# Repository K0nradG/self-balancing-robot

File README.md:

# Self-Balancing Robot

A two-wheeled self-balancing robot built around the **Nordic nRF52840** and
**Zephyr RTOS**, using **nRF Connect SDK 2.8.0**. The project includes the
embedded control system, custom electronics and mechanical designs, a BLE
desktop application, over-the-air firmware updates, and tools for modelling
and controller development.

## Documentation

- [Project overview](README.md)
- [Environment setup](docs/environment_setup.md)
- [Building and flashing](docs/building_and_running_fw.md)
- [BLE protocol](Sources/drivers/bluetooth/README.md)
- [Control-loop structure](Sources/robot_control/docs/control_loop.md)
- [Application state machine](Sources/robot_control/docs/application_state_machine.md)
- [Mathematical model](mathematical_model/doc/model.md)

## Demonstration

https://github.com/user-attachments/assets/bdc0d3e3-bf6b-4125-bade-0684ad42b085

> 🎥 **See the robot in action!** 
> Check out the [Lapun Embedded Control Lab](https://youtube.com/@lapunembededcontrollab) on YouTube for more demonstrations.
>
> 

## Features

### Robot firmware

- Cascaded control loop for balancing, driving, and rotation
- PID controllers with user-adjustable setpoints and parameters
- Optional LQR balance controller
- Trajectory generation for linear motion and rotation
- MPU6050 inertial measurement and quadrature encoder feedback
- PWM motor control through a dual-channel TB6612FNG driver
- Battery-voltage monitoring
- Safety angle validation and controlled motor shutdown
- Binary BLE protocol for commands, telemetry, and diagnostic logs
- MCUboot-based device firmware update over BLE

### Control and development tools

- PyQt6 desktop application for BLE control, live telemetry, PID tuning, and DFU
- Offline model identification and LQR tuning tools
- MATLAB/Simulink models of the inverted-pendulum system
- Optional Raspberry Pi Zero 2 W web interface with camera streaming
- KiCad schematics, PCB layout, Gerber files, and mechanical CAD

> [!NOTE]
> The default firmware configuration uses PID control. The LQR controller and
> on-device model-identification mode are implemented but disabled by default.
>
> The Raspberry Pi web interface and the nRF7002 DK controller are legacy or
> experimental components and may require adaptation to the current binary BLE
> protocol.

## Control architecture

The firmware uses a cascaded control structure. Distance and linear-speed
controllers generate the balance-angle setpoint, while the balance and
rotation controllers determine the wheel-speed setpoints. Separate wheel
controllers then generate the motor PWM outputs.

## Hardware

The robot is based on:

- Nordic nRF52840 Dongle
- MPU6050 IMU
- Two DC gearmotors with quadrature encoders
- TB6612FNG dual motor driver
- 2-cell, 7.4 V LiPo battery
- Custom PCB and 3D-printed mechanical structure
- Optional Raspberry Pi Zero 2 W and CSI camera

Hardware design files are available in [`Schematic/`](Schematic/).

### Custom PCB

<p align="center"><em>3D render of the custom robot controller PCB.</em></p>

## Getting started

### Prerequisites

- [nRF Connect SDK 2.8.0](https://developer.nordicsemi.com/nRF_Connect_SDK/doc/2.8.0/nrf/index.html)
- nRF Connect toolchain 2.8.0
- West and the Zephyr development environment
- An external SWD debugger for the initial firmware installation

Follow the [environment setup guide](docs/environment_setup.md) before
building the project.

### Build the robot firmware

From the repository root:

```bash
cd Sources/applications/app
west build -b nrf52840dongle_nrf52840 -p always
```

A successful build generates:

```text
Sources/applications/app/build/merged.hex
Sources/applications/app/build/dfu_application.zip
```

The firmware can also be built through nRF Connect for VS Code. See
[Building and flashing](docs/building_and_running_fw.md) for the complete GUI,
terminal, SWD, and BLE DFU workflows.

### Flash the initial firmware

After connecting an external SWD debugger:

```bash
cd Sources/applications/app
west flash --erase --skip-rebuild
```

Subsequent firmware versions can be installed over BLE using the desktop
application or the command-line DFU tool.

### Run the desktop application

The desktop application requires Python 3, PyQt6, Bleak, and PyQtGraph:

```bash
python3 -m pip install PyQt6 bleak pyqtgraph
python3 run_controller_app.py
```

The DFU workflow additionally requires
[`smpmgr`](https://github.com/intercreate/smpmgr). A Windows binary is included
in [`3rdParty/smpmgr/`](3rdParty/smpmgr/); on Linux, `smpmgr` must be available
on `PATH`.

## Repository structure

```text
.
├── Sources/applications/app/          # Main nRF52840 robot firmware
├── Sources/applications/controller/   # Experimental nRF7002 DK controller
├── Sources/applications/controller_rpi/
│                                      # Raspberry Pi web interface
├── Sources/drivers/                   # IMU, encoders, motors, BLE, DFU, battery
├── Sources/robot_control/             # Control loop, PID, LQR, state machines
├── robot_control_app/                 # PyQt6 BLE desktop application
├── mathematical_model/                # Models, identification, and LQR tooling
├── Schematic/                         # PCB, schematics, Gerbers, and CAD
├── docs/                              # Setup and build documentation
└── dts/bindings/                      # Custom Zephyr devicetree bindings
```

## Roadmap

- Swing-up procedure
- Neural and other intelligent controllers
- Vision-based autonomous navigation

## Licensing

- Software and firmware: [Apache License 2.0](LICENSE)
- Hardware designs (schematics, PCB, and CAD):
  [CERN-OHL-P-2.0](Schematic/LICENSE)

Commercial use is permitted under the terms of the respective licenses.

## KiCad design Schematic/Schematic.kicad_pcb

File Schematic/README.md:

## License

This project is licensed under the **CERN Open Hardware Licence Version 2 - Permissive (CERN-OHL-P)**. 

The license covers all design files in this directory, including:
* **Electronics:** KiCad schematics, PCB layouts, and libraries.
*  **Mechanics:** Physical case design (Fusion 360 files in the `robot-case` directory).

Copyright © 2026 Dymczyk Filip and Konrad Grucel

# **Project Based on KiCad 7.0**

## **Generating Gerber Files**

To generate new Gerber files after making changes to the schematic, follow [this guide](https://jlcpcb.com/help/article/how-to-generate-gerber-and-drill-files-in-kicad-7).

### **Quick Guide**

1. Open the PCB editor.
2. Click **File → Fabrication Outputs → Gerber Files (.gbr)**.
3. Your configuration should look like the following image:

4. Click **Plot**, and the files will be saved in your selected output directory.

For drill files **.drl**, follow these steps:

1. Configure settings as shown below:

1. Click **Generate Drill Files**, then **Generate Map Files**.
2. The files will be saved in your selected output directory.

**Adding Custom Symbols, Footprints, and 3D Models**

### **Sources for Custom Components**

You can find various custom symbols, footprints, and 3D models online. Recommended sources:

- [GrabCAD](https://grabcad.com/library/lm2596-module-for-kicad-1)
- [SnapEDA](https://www.snapeda.com/parts/GY-521/GODREAM FORDREAM CO., LIMITED/view-part)

All external symbols, footprints, and 3D models used in this project are located in the `external-3d-models` and `external-symbols-footprints` directories. The sources for these components are documented in `utils/external-parts-Kicad.txt`.

### **Adding Symbols and Footprints**

#### **1. Download the Files**

Example files from [SnapEDA](https://www.snapeda.com/parts/GY-521/GODREAM FORDREAM CO., LIMITED/view-part):

- **Symbol:** `.kicad_sym`
- **Footprint:** `.kicad_mod`

#### **2. Adding a Symbol**

1. Open the KiCad schematic editor.
2. Click **Preferences → Manage Symbol Libraries**.
3. Click the folder icon and provide the path to the `.kicad_sym` file.

#### **3. Adding a Footprint**

1. Open the KiCad schematic editor.

2. click the following icon

3. Click **Preferences → Manage footprints Libraries**,  and provide an path to the `.kicad_mod` file

next you have to click `Preferences button` button and then `Manage footprints liblaries`

then you have to click `directory(folder)` icon and provide a path to your `.kicad_mod` file.

**note: ** the `kicad_mod` and `kicad_sym` files can be in the same directory. if you download footprint and symbol package.

## **Adding 3D Models**

1. Download a 3D model, for example, from [GrabCAD](https://grabcad.com/library/mpu-6050-imu-sensor-1).
2. Place the corresponding symbol in the schematic.
3. Open the PCB editor and click **Tools → Update PCB from Schematic**.
4. Once the component appears, double-click it.
5. Navigate to the **3D Models** tab and provide the path to the `.wrl` or `.step` file.

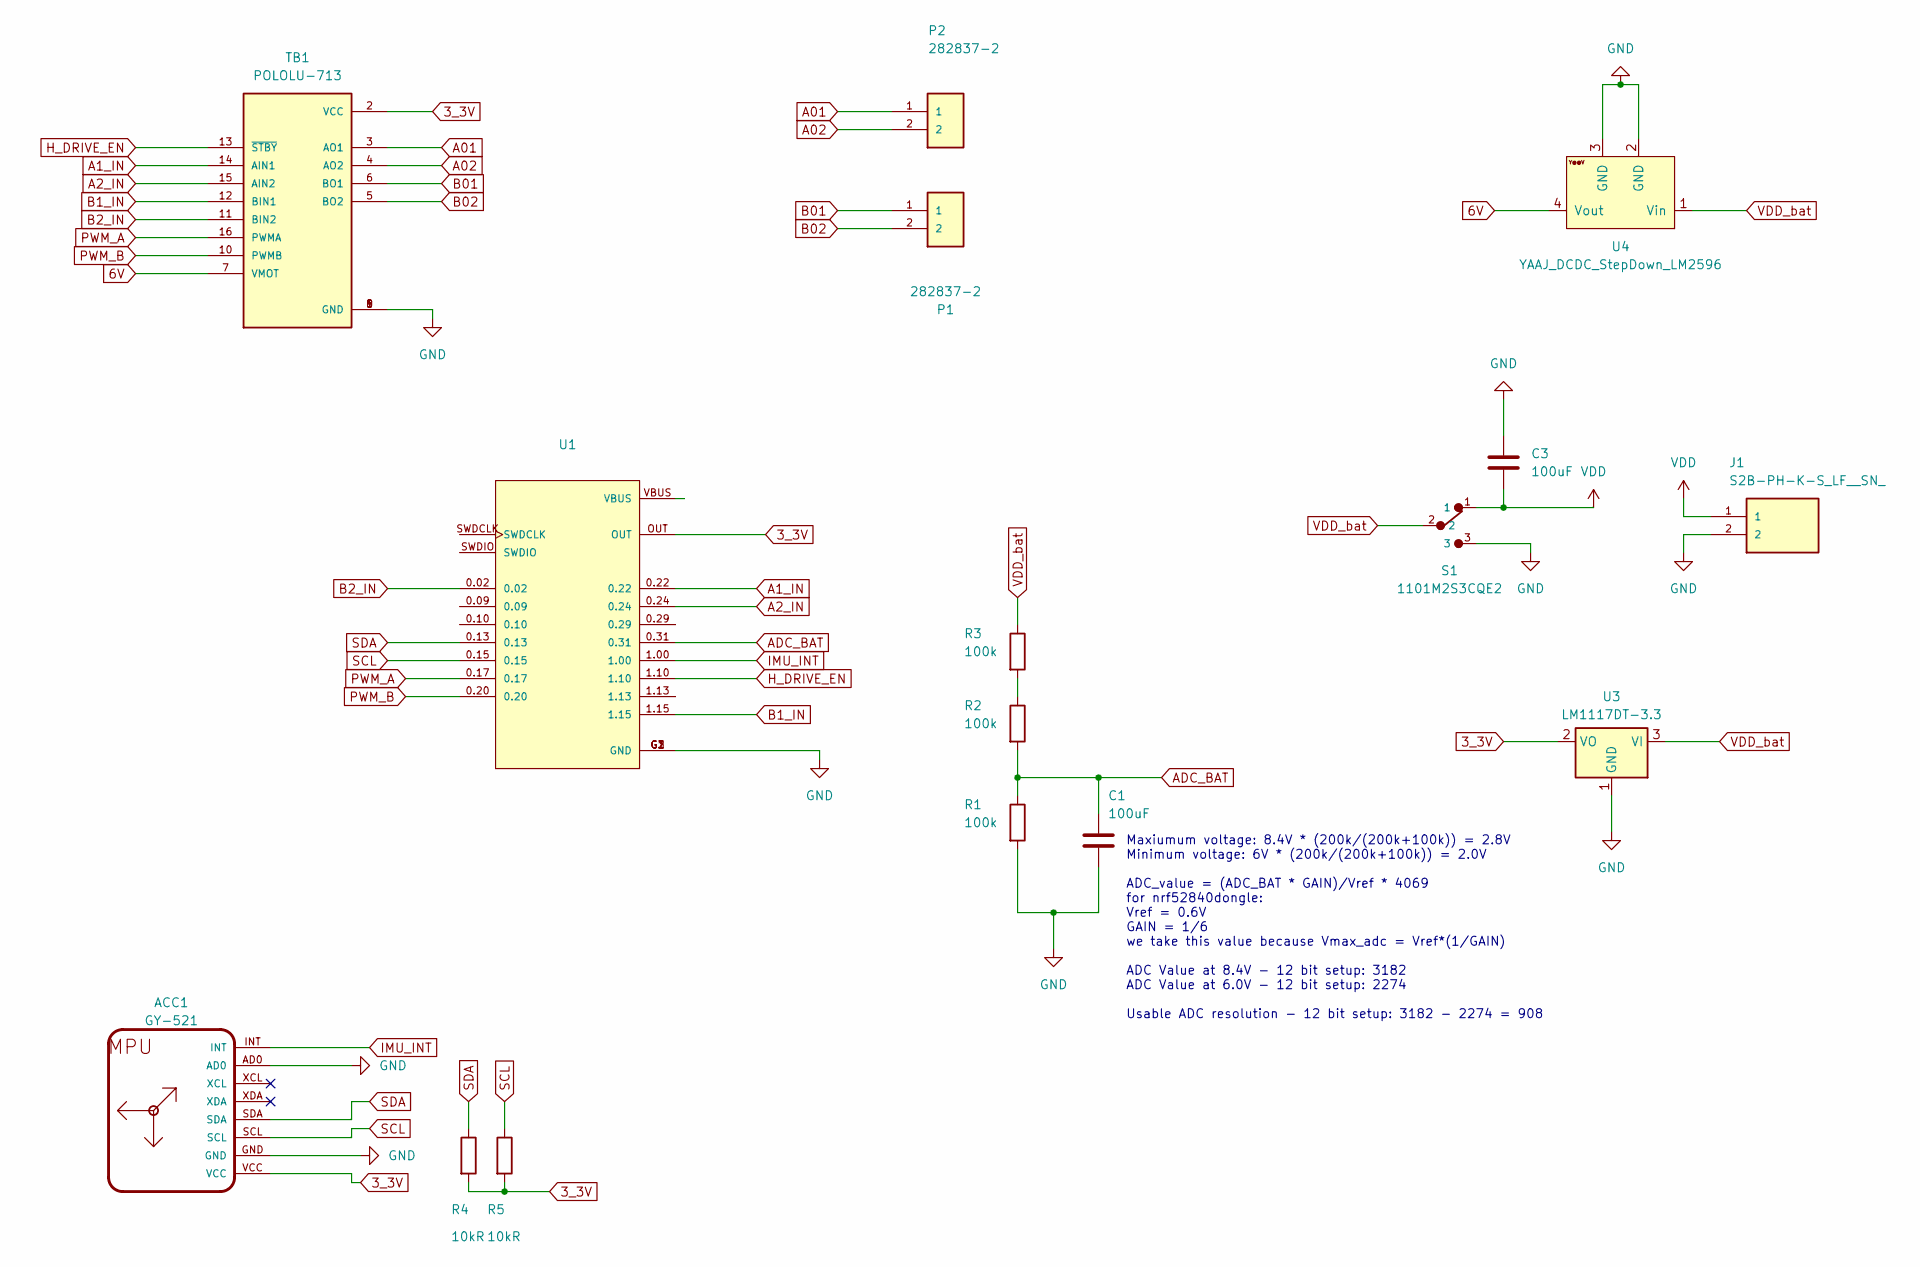
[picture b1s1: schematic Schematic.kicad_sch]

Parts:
ACC1: GY-521
C1, C3: 100uF; C_Disc_D7.5mm_W4.4mm_P5.00mm
J1: S2B-PH-K-S_LF__SN_; JST_S2B-PH-K-S_LF__SN_
P1, P2: 282837-2; TE_282837-2; PARTREV G3
R1, R2, R3: 100k; R_Axial_DIN0207_L6.3mm_D2.5mm_P5.08mm_Vertical
R4, R5: 10kR; R_Axial_DIN0207_L6.3mm_D2.5mm_P5.08mm_Vertical
S1: 1101M2S3CQE2; SW_1101M2S3CQE2
TB1: POLOLU-713; SHIELD_POLOLU-713
U1: NRF52840-DONGLE; MODULE_NRF52840-DONGLE
U3: LM1117DT-3.3; TO-252-3_TabPin2
U4: YAAJ_DCDC_StepDown_LM2596

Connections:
3_3V: ACC1.VCC, R4.2, R5.2, TB1.2 (VCC), U1.OUT, U3.2 (VO)
6V: TB1.7 (VMOT), U4.4 (Vout)
A01: P2.1, TB1.3 (AO1)
A1_IN: TB1.14 (AIN1), U1.0.22
A02: P2.2, TB1.4 (AO2)
A2_IN: TB1.15 (AIN2), U1.0.24
ADC_BAT: C1.1, R1.1, R2.2, U1.0.31
B01: P1.1, TB1.6 (BO1)
B1_IN: TB1.12 (BIN1), U1.1.15
B02: P1.2, TB1.5 (BO2)
B2_IN: TB1.11 (BIN2), U1.0.02
GND: ACC1.AD0, ACC1.GND, C1.2, C3.1, J1.2, R1.2, S1.3, TB1.1 (GND), TB1.8 (GND), TB1.9 (GND), U1.G1 (GND), U1.G2 (GND), U1.G3 (GND), U3.1 (GND), U4.2 (GND), U4.3 (GND)
H_DRIVE_EN: TB1.13 (~STBY), U1.1.10
IMU_INT: ACC1.INT, U1.1.00
unnamed: R2.1, R3.2
PWM_A: TB1.16 (PWMA), U1.0.17
PWM_B: TB1.10 (PWMB), U1.0.20
SCL: ACC1.SCL, R5.1, U1.0.15
SDA: ACC1.SDA, R4.1, U1.0.13
VDD: C3.2, J1.1, S1.1
VDD_bat: R3.1, S1.2, U3.3 (VI), U4.1 (Vin)

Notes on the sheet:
Maxiumum voltage: 8.4V * (200k/(200k+100k)) = 2.8V Minimum voltage: 6V * (200k/(200k+100k)) = 2.0V ADC_value = (ADC_BAT * GAIN)/Vref * 4069 for nrf52840dongle: Vref = 0.6V GAIN = 1/6 we take this value because Vmax_adc = Vref*(1/GAIN) ADC Value at 8.4V - 12 bit setup: 3182 ADC Value at 6.0V - 12 bi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

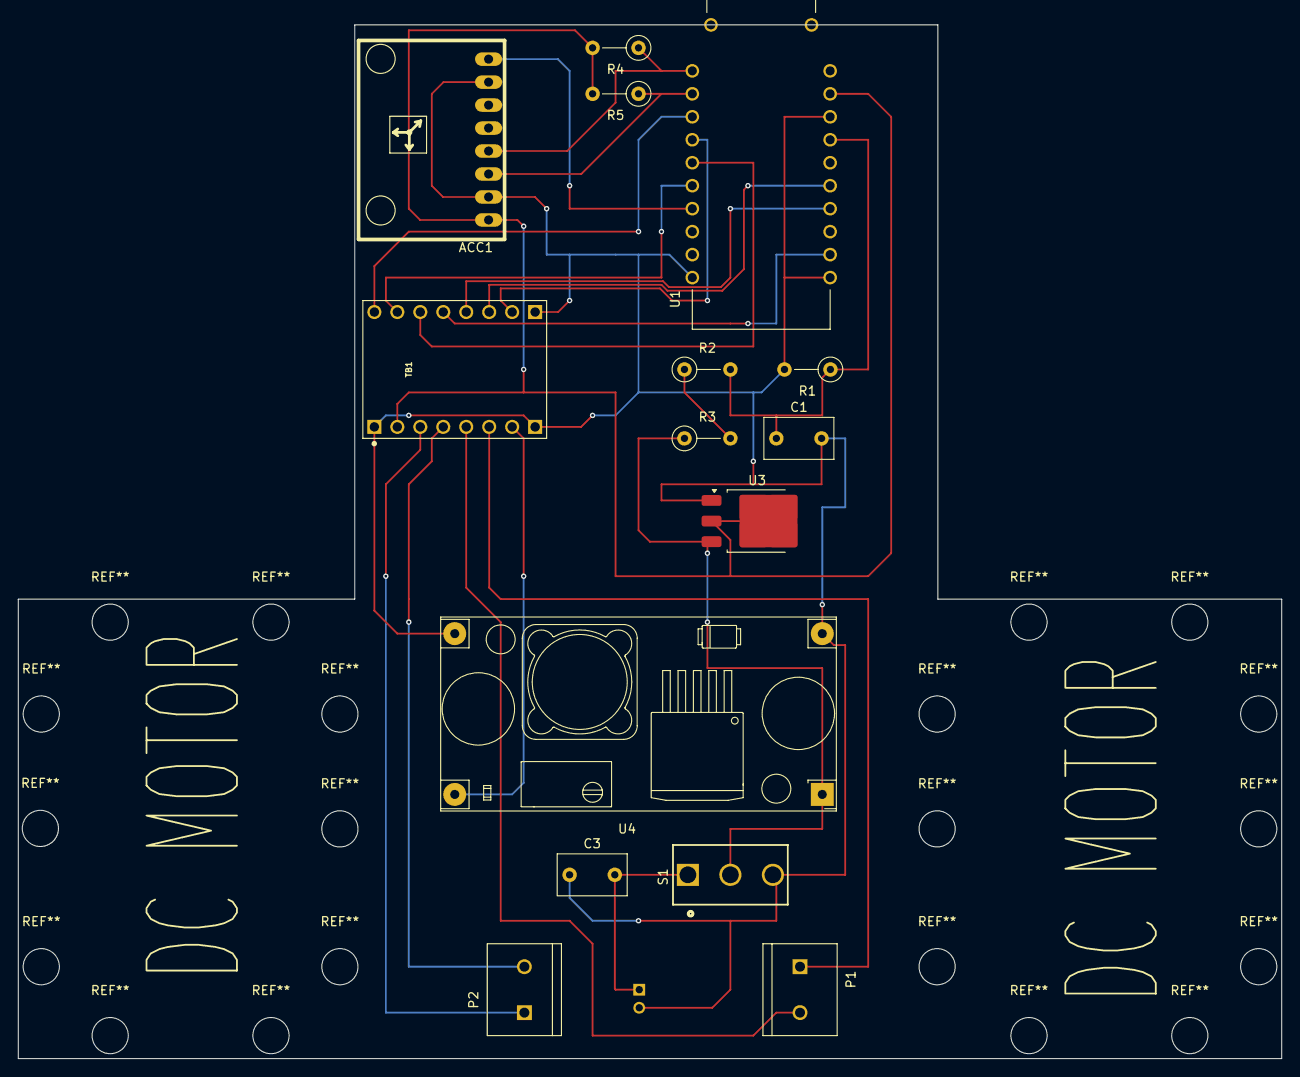
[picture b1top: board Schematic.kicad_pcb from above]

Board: 2 copper layers, 139.7 x 114.3 mm, 16 parts (1 on the bottom side), 21 nets.

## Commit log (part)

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2025-02-03 PCB: KiCAD setup
    -create kicad project
    -add footprints,symbols and 3d models of nrf52840dongle and MPU 6050
2025-02-04 PCB: adding the required symbols, footprints and 3D models
    - create generic paths to the symbos and footprints, so there is no problem with setup on the other machine
    - adding further PCB elements of the project
2025-02-06 PCB: Basic schematic.
2025-02-07 PCB: completing the electrical diagram
    -fix with the H bridge (we have to use TB6612FNG which can operate at PWM 3.3 V
    -complete schematic
    -create prototype PCB schematic
    -track PCB paths
2025-02-07 PCB: add schematic pdf
2025-02-07 PCB; kicad doc
    -fix with link to the snapeda
2025-02-07 App: Setup dummy app
2025-02-08 App: small structure fixes
    -include batteryu_level.h only if CONFIG_BATTERY_LEVEL_DRV=y
    -delete uceecesseray comments
2025-02-08 App: add doc
    -describe how to setup environment
    -describe how to build an app
    -describe how to flash nrf52840dongle
2025-02-09 Drivers: battery_level
    -crate an api for periodic battery level measurements
    -create an doc with appropriate description
    -use the created api in main app
2025-02-09 App: add configuration for battery drv
    -add configuration which enable building witch CONFIG_BATTERY_LEVEL_DRV=n
    or CONFIG_BATTERY_LEVEL_DRV=y
2025-02-09 Creating utils directory to be used for drivers.
2025-02-09 Motor controller driver scheme.
2025-02-09 GPIO mapping done.
2025-02-11 Minor fix.
2025-02-12 PWM and GPIO configuration done.
2025-02-12 Minor overlay change.
2025-02-13 Drivers: Battery_level driver fix
    -make a configuration which enables to perform adc mesaurements
2025-02-14 Excessive clangd compilation warnings fix.
2025-02-17 Ignoring compile_commands.json.
2025-02-22 Comments resolution.
2025-02-23 Stop trakcing .vscode.
2025-02-27 Drivers: imu
    -imu_refactoring - give data to user by callback with data structure
    -create regulator as a driver
    -regulator params can be updated with nus
    -create an callback which presents new params
2025-02-27 Regulator and IMU working with NUS.
2025-02-27 Callback registering in main.
2025-02-28 Added config for PWM limit.
2025-02-28 DPFL setting seems to work.
2025-03-01 Asyncrhonous motor controlled worker called by regulator. Adjusted PWM period and regulator worker interval.
2025-03-01 Motors direction based on error sign, not output.
2025-03-01 Derivative filtering and integral anti-windup.
2025-03-02 Drivers: model identyfication driver
    -add driver which enables send input,angle,angular acceleration and time over serial
2025-03-04 Script for receiving serial data directly. Directories tidy up.
2025-03-04 Scripts: Identification
    -write a script which calcualte inverse pendulum model based on aggle, angle_dt, u and time arrays
    -add doc
2025-03-05 State machine for repeatable identification.
2025-03-05 Scripts: new identification data
2025-03-07 Inverted pendulum modeled, with description and scripts adjustments.
2025-03-10 model.md update.
2025-03-10 identification.md distinguished from model.md, introduced script for closed loop identification and obtaining of discrete model.
2025-03-10 Script fix.
2025-03-10 LQR initial testing, PID tuning in simulation.
2025-03-11 Further identification/tuning work.
2025-03-12 Tidy up.
2025-03-13 .gitignore update
2025-03-13 Conditional compilation of regulator types. More generic callbacks - simplification.
2025-03-16 App: find stable configuration - robot is balancing
    - Adjust acc and gyro ranges
    - turn off dlpf
    - turn off setting mresurement interval
    - adjust PID gains
    - adjust setpoint
    - try to adjust ALPHA parameter of complementarny filter
2025-03-17 Closed loop identification with fminsearch and RK4. Introduced necessary matlab functions. Scripts adjustments.
2025-03-18 Regulator: PID
    -find otimal gains values
2025-03-23 Test scripts for various sensor merging filters.
2025-04-01 IMU: fixes cd
    -change parameters
2025-04-01 IMU/regulator: to do list
2025-04-15 adjsuting PID
2025-05-06 PID: compensate DC engine deadzone
    -to do:
    - change DC voltage
    - adjust PID params
2025-05-21 Data collected for identification with new stabilizing P.
2025-05-23 Rest of the repor tidy up.
2025-05-25 Introducement of IMU angle software filtering, with tests on collected data.
2025-05-26 Matlab files tidy-up
2025-05-26 Preparing for rotation control
2025-05-29 applications:controller
    -added controller app based on nrf7002DK which enable to control
    the rotate angle of an robot using dwo buttons placed on the DK
    -nrf7002DK works as BLE central
    -controller is sending appropriate messeages which are simple text
    commands which are sending over BLE using NUS to the balancing robot
2025-06-01 applications:controller: added rotate commands
    -refactor motor controller dirver, now setting direction is not neacceseary anmore it is set based on the set pwm value
    -adjust balance and rotate PID gains
    -change the logic of performing rotates - it is based on the one worker
2025-06-01 application:controller & app
    -disable logs from app - some strange performance after disabling,
    robot the robot falls backwards, check if it is because of
    some timings due to disabling logs or just lower batter level
    -added logic do controller which allow to mow +-40 degrees by
    clicking arrows on the laptop
2025-06-02 Applications:controller: rotate angle being set using potentiometer
2025-06-03 applications:controller: setting angle using ramp
2025-07-09 tools: simplify updating dongle firmware via USB DFU
    It's no longer necessary to use the nRF Programmer GUI.
    Firmware update can now be done using the flash.py script.
    The script runs inside a Docker container to ensure compatibility with the correct Python version required by nrfutil.
    This avoids Python version conflicts on the host system (especially on distributions like Linux Mint ;) ).
2025-07-17 drivers: encoder driver
    -added distance calculation
    -added absolute rotate angle calculation
2025-07-22 Initial cpp migration for PID and general controller
2025-07-23 Further control logic migration
2025-07-23 Min/max fix
2025-07-24 drivers: regulator
    -control loop is trigered by imu module
2025-07-26 drivers: regulator
    -trigger enkoder update work by robot controller
2025-07-26 drivers: NUS
    -fixed nus parsing
2025-07-27 drivers: general clean up
    -added DataManager singleton to manage data
2025-07-31 Small fix
2025-08-10 IMU improvements
2025-08-10 API for: setting new low-pass filter alpha coeff and using direct fedback derivative as input for D part of PID controller
2025-08-11 Failed IMU data fetch protection
2025-08-11 Files with code under Sources directory; introduction of build scripts for selected boards
2025-08-12 Bluetooth driver decoupling from logger driver; removed particular zephyr inits from drivers in favor of introducing a global Drivers_Initializer class
2025-08-19 State machine to control the stopping/starting of the robot with the use of a button
2025-08-31 Watchdog driver
2025-09-04 Encoderss angle combined with gyro data to acquire rotation angle; build scripts with changed files formatting
2025-09-17 app: enable dfu ble smp
    -added mcuboot bootloader
    -disable nrf5sdk bootloader
    -added dfu ble configuration
    -added shell command for getting firmware version
2025-09-25 parameters: params adjustment
2025-09-28 newtmgr integration
2025-10-07 dfu state machine
2025-10-11 app: added app version ble command
2025-10-16 Added state machine NUS commands instead of button pressing
2025-10-16 app: dfu refinments
2025-10-20 Wheels speed regulator seems to have nice result - braking when too much speed e.g.
2025-10-22 Critical bug with PID hysteresis approach fix
2025-10-27 Ramp class introduced with rotate setpoint ramping
2025-10-28 Initial distance controller implementation - stays in place and follows setpoint (can overshoot - to be tuned)
2025-10-30 ble: optimize negotaion process for NUS and dfu
2025-10-30 controller_rpi:added app dashboard
2025-10-30 Linear speed PID control - robot drives with constant speed, braking when reaching target (small overshoot)
2025-10-31 Additional state machine improvements/protections against invalid input
2025-11-01 Trajectory manager enhanced with dedicated state machine
2025-11-02 set ble device name in prj.conf
2025-11-02 web server accepts .zip dfu files
2025-11-02 robot control: added nus logs clock divider
2025-11-02 controler_rpi: wait for trajectory ack from device
2025-11-02 controler_rpi: edit buttons visibility on the dfu dashboard
2025-11-02 controller_rpi: added back button on app_dashboard.html
2025-11-02 controller_rpi/app: prepare app and controller_rpi for trajectory communication
    - added nus callback which is being called after "tc" command is send from device
    - complete the logic in the montion.html - we send trajectory command after recieving "tc" command
2025-11-02 controller_rpi: wait forever for device ack
2025-11-04 Robot controller parsing now allows to enter multiple messages in one data - parsing happening until all data is handled
2025-11-17 Logging reworking
2025-11-18 Restoring comments and additional improvements
2025-12-01 PID regulator params sending (initial) through NUS
2025-12-06 Robot controller as a singleton
2025-12-07 controller_rpi: adjust delay time to get data from robot
2025-12-07 controller_rpi: send separate setting params commands for each reagulator
2025-12-07 controller_rpi: save regulators gains in persistent storage
2025-12-07 controller_rpi: added manual scroll on app_dashborad.html
2025-12-08 Swing-up in Main_State_Machine with distance controlling disabling/enabling
2025-12-09 Motors disabling command can be requested from every state and is handled in the first place
2025-12-09 Minor changes
2025-12-09 controller_rpi: added swing-up start button
    - extend safe angle ranges for wing-up and balnce stages
    - reset encoders after swing-up
2025-12-10 controller_rpi: added battery level guard
2025-12-12 app: simplify identification module API
2025-12-12 app: added identification driver to Robot_controll namespace
2025-12-13 app: added open loop configuration while identification module is on
2025-12-14 controller_rpi: added identification interface
2025-12-14 app/contrller_rpi: integrate UI with app
2025-12-15 controller_rpi/app: extend identification data
2025-12-16 app: achieve stable sampling time 50ms for identification
2025-12-18 app: sends identification data over uart
    -adjust .ovelray
    -adjust stack sizes to handle ble and uart stacks
2025-12-18 app: remove cts/rts urat pins to not ovelray with a-in h bridge control pins
2025-12-28 Initial clean-up
2025-12-28 Robot_Controller methods dividing; better State_Machine behavior with model_identification
2025-12-28 Small improvements - large structs returned by reference
2026-01-19 model identification : adjust logging sample time
2026-01-21 model_identification: increase the uart baudrate to speed up sending the data
    - TO DO:
    - make sapling time stable (now it is oscilating a little bit betweeen 6 and 7ms)
2026-02-02 Markdowns tidy-up, unused files removal and licenses adding
2026-02-21 mathematical model: added identification process description
2026-02-21 mathematical_model: delete old data
2026-02-21 mathematical_model: added LQR control signal plotting
2026-02-22 mathematical_model: code cleanup
2026-02-28 mathematical model: initial LQR test derived from mathematical model
    -there was need to zero the angle_dt state gain - it is need to be filtered
2026-03-15 controler_rpi: minior fixes
2026-03-22 License: minior fixes
